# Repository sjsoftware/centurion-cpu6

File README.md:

# centurion-cpu6

* Schematic of the Centurion CPU6 board
* Schematic of the Centurion CPU5 boards
    * Original plus some revisions 
* Microcode disassembly (plus on wiki)
* Instruction reference (on wiki)
* Whatever I add in

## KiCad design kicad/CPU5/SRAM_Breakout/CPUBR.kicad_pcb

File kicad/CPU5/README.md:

# CPU 5 Reverse Engineering

Use at your own risk

The schematics are a bit of a mess, I wanted to get them to fit on A1 paper. If you have suggestions for
improvement, raise an issue.

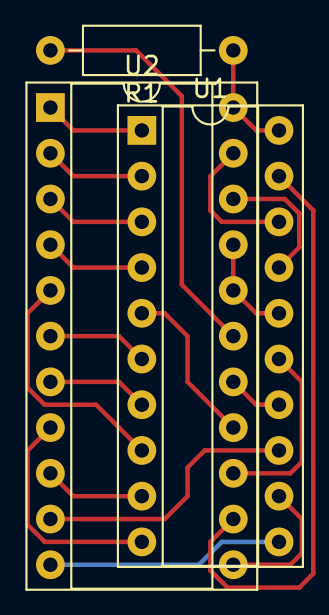
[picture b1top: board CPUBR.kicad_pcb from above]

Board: 2 copper layers, 3 parts (0 on the bottom side), 21 nets.

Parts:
R1: 1k; R_Axial_DIN0207_L6.3mm_D2.5mm_P10.16mm_Horizontal
U1: 74LS208; DIP-20_W7.62mm_Socket
U2: 93L422; DIP-22_W10.16mm_Socket

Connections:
GND: U1.10 (GND), U2.8 (GND)
unnamed: U1.11 (D0), U2.11 (D1)
unnamed: U1.14 (Q2), U2.16 (Q3)
unnamed: U1.16 (~OE), U2.18 (~OE), U2.19 (~CS1)
unnamed: U1.17 (WE), U2.20 (~WE)
unnamed: U1.18 (A7), U2.21 (A4)
unnamed: U1.19 (D3), U2.13 (D2)
unnamed: U1.1 (A0), U2.1 (A3)
unnamed: U1.2 (A1), U2.2 (A2)
unnamed: U1.3 (A2), U2.3 (A1)
unnamed: U1.4 (A3), U2.4 (A0)
unnamed: U1.8 (A6), U2.5 (A5)
unnamed: U1.6 (A4), U2.6 (A6)
unnamed: U1.7 (A5), U2.7 (A7)
unnamed: U1.9 (D1), U2.9 (D0)
unnamed: U1.13 (Q1), U2.10 (Q0)
unnamed: U1.12 (Q0), U2.12 (Q1)
unnamed: U1.15 (Q3), U2.14 (Q2)
unnamed: U1.5 (D2), U2.15 (D3)
unnamed: R1.2, U2.17 (CS2)
VCC: R1.1, U1.20 (VCC), U2.22 (VCC)

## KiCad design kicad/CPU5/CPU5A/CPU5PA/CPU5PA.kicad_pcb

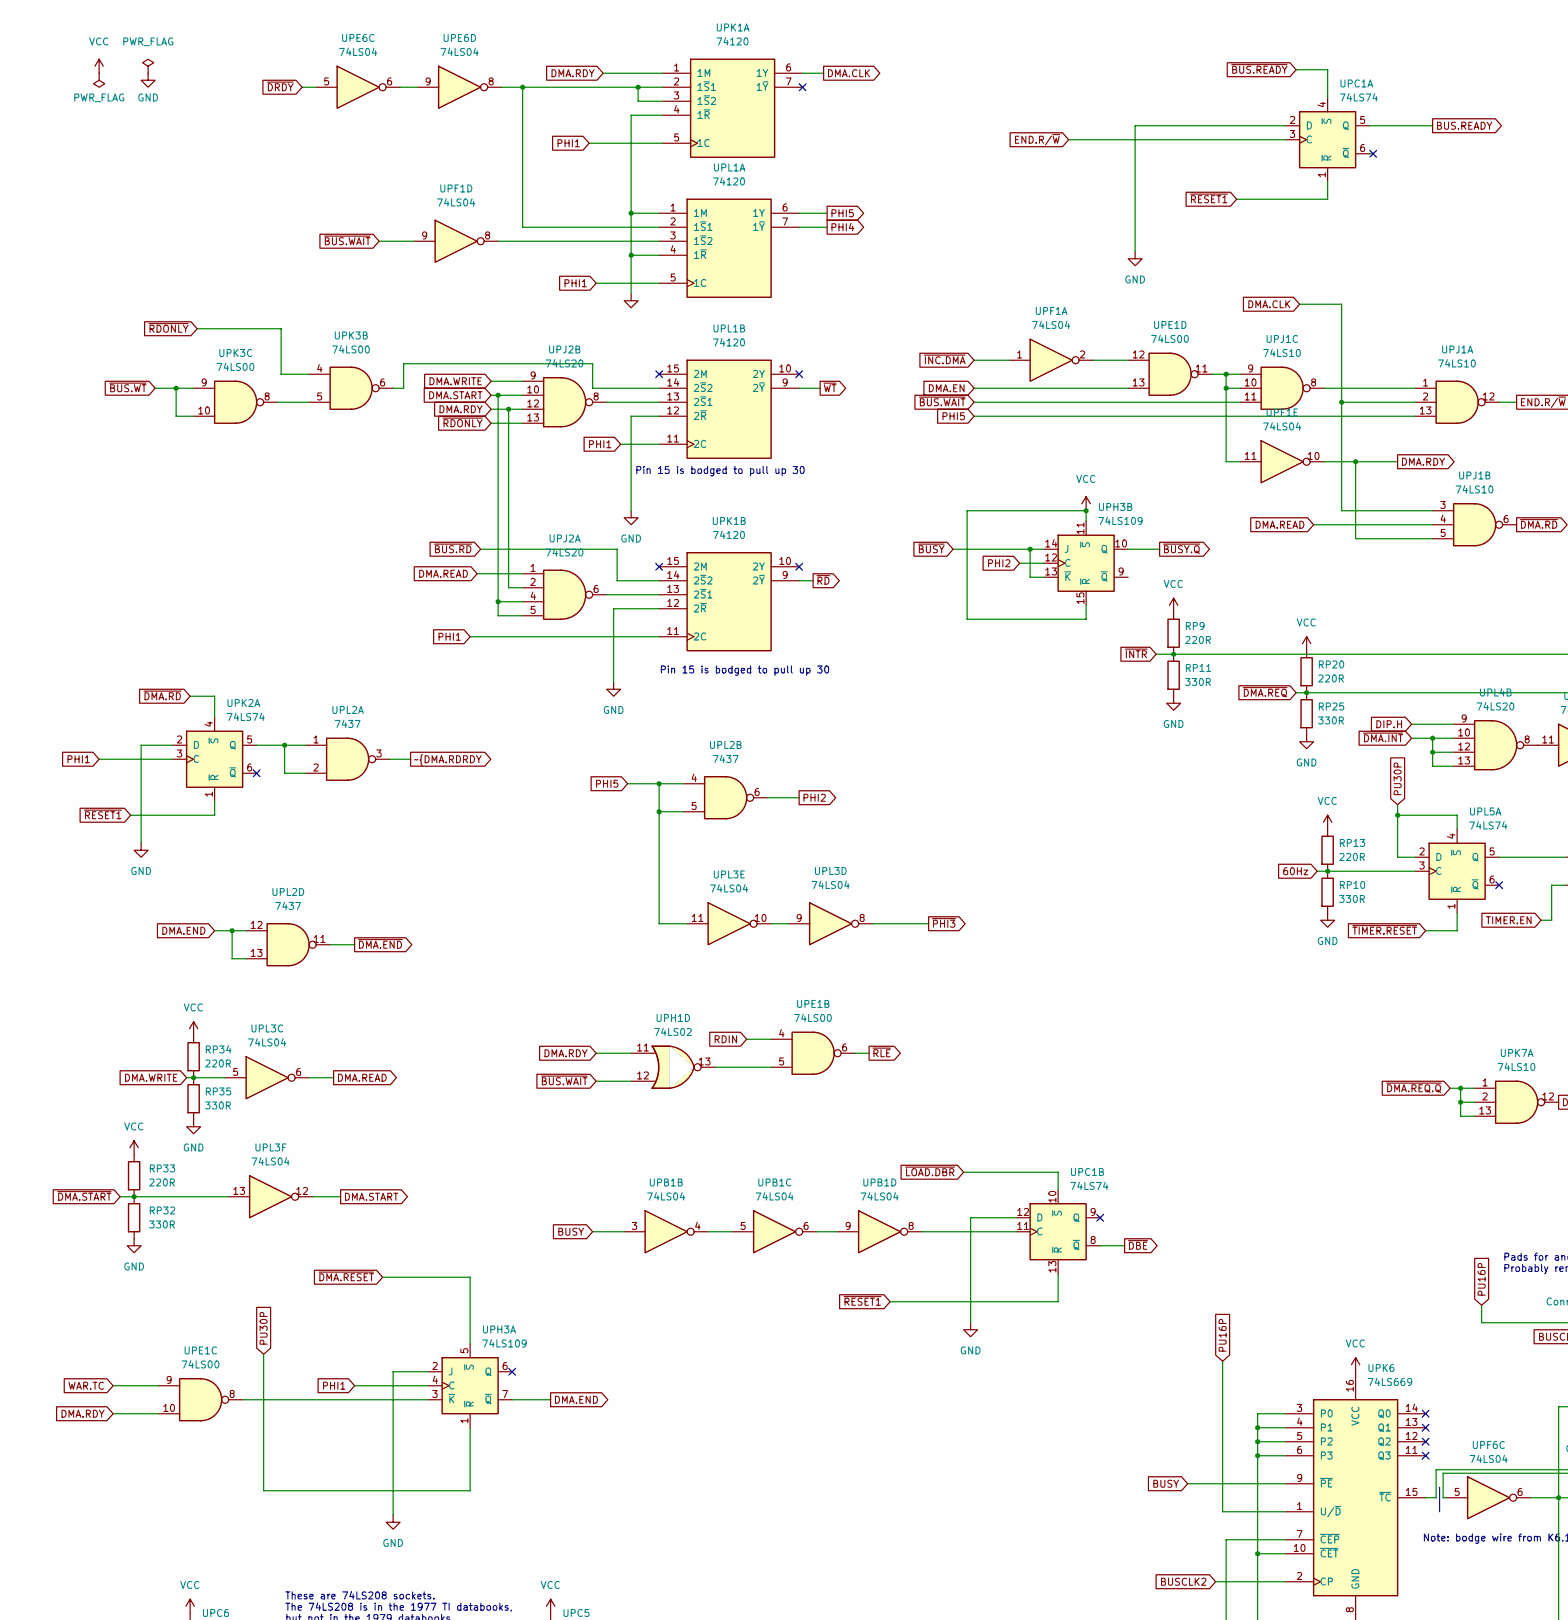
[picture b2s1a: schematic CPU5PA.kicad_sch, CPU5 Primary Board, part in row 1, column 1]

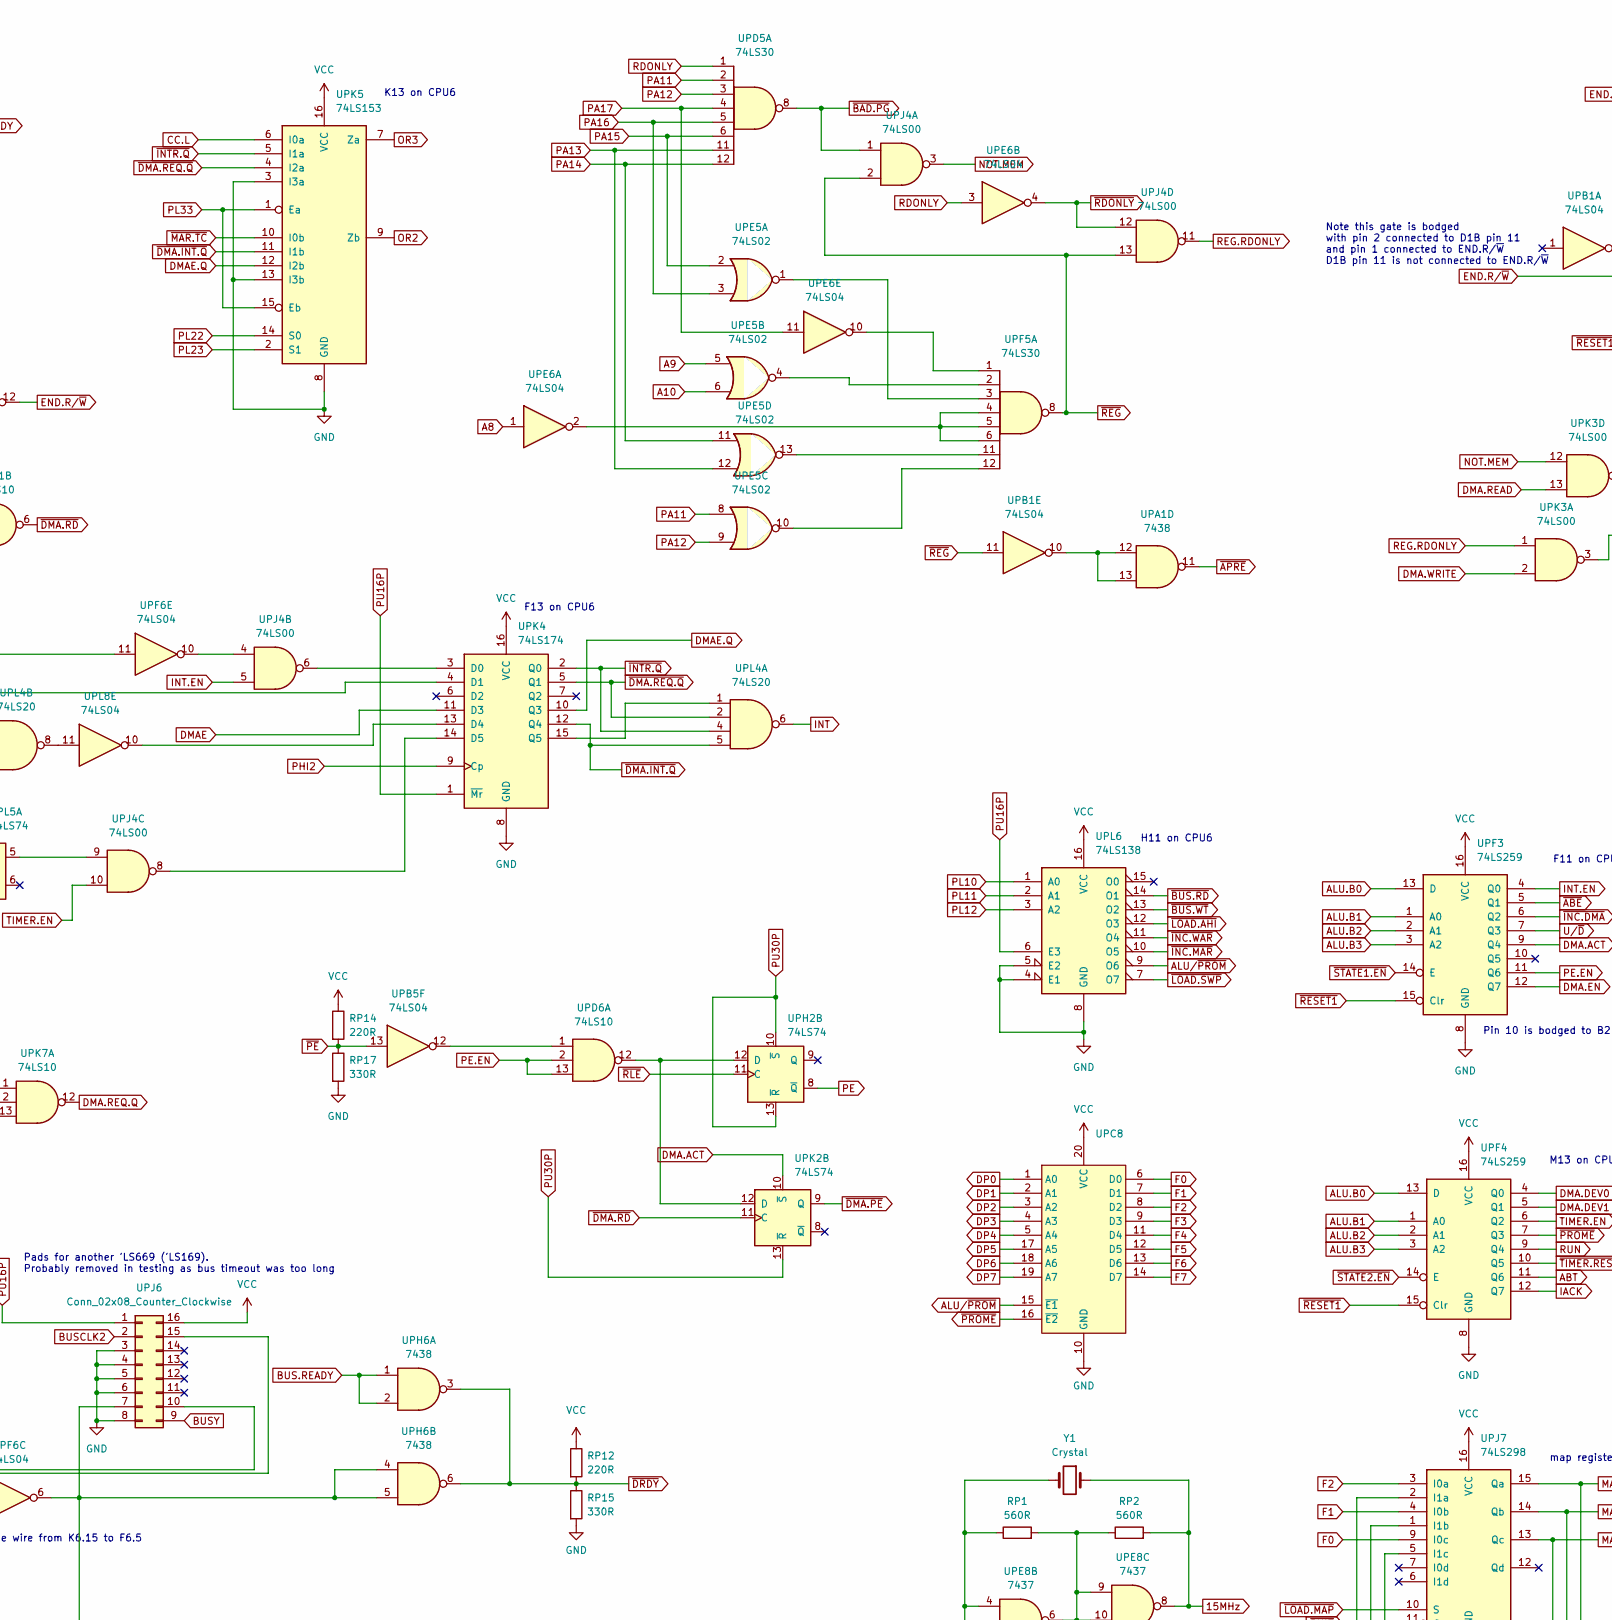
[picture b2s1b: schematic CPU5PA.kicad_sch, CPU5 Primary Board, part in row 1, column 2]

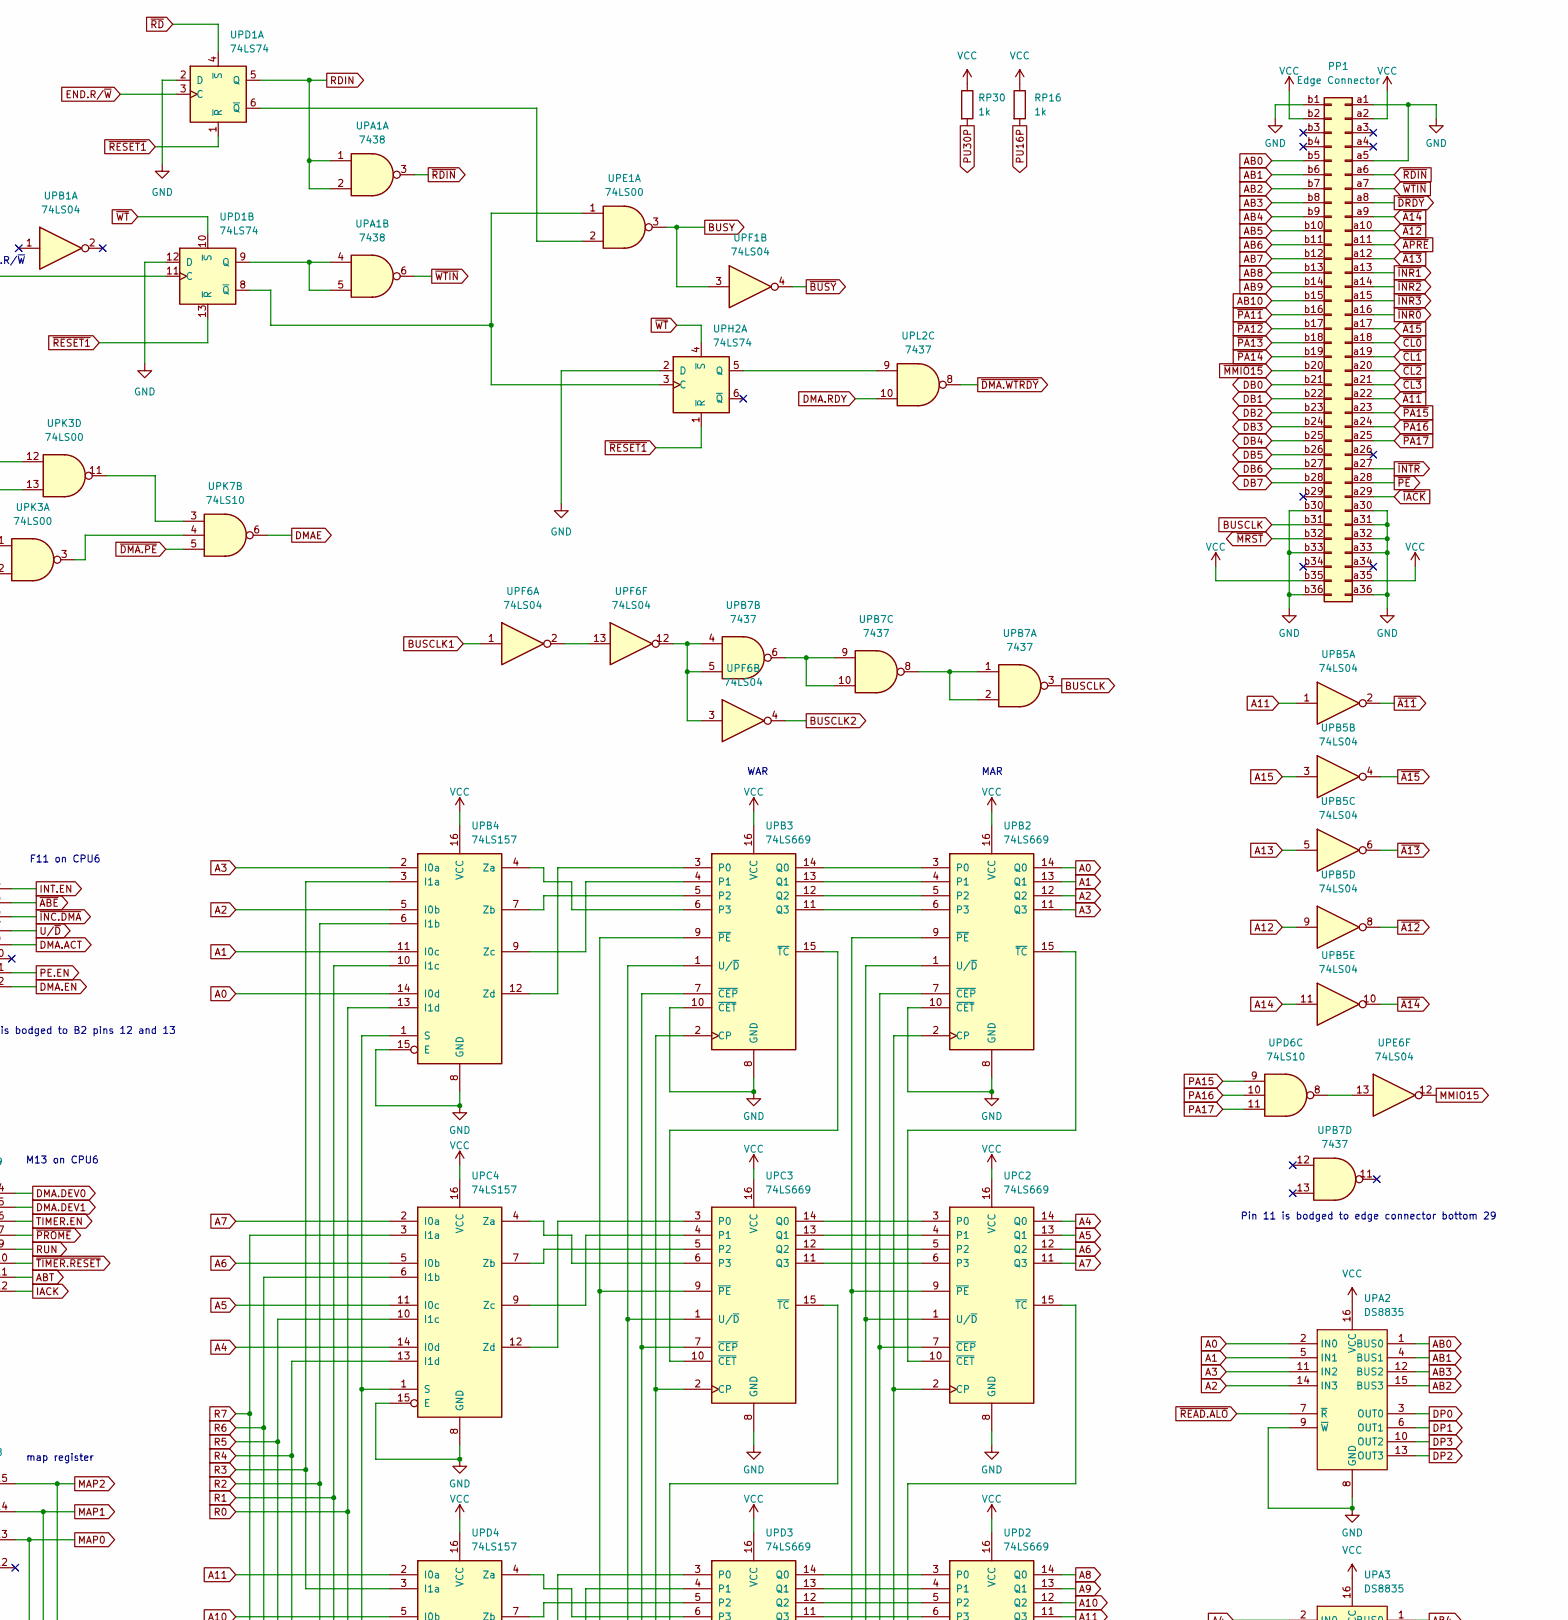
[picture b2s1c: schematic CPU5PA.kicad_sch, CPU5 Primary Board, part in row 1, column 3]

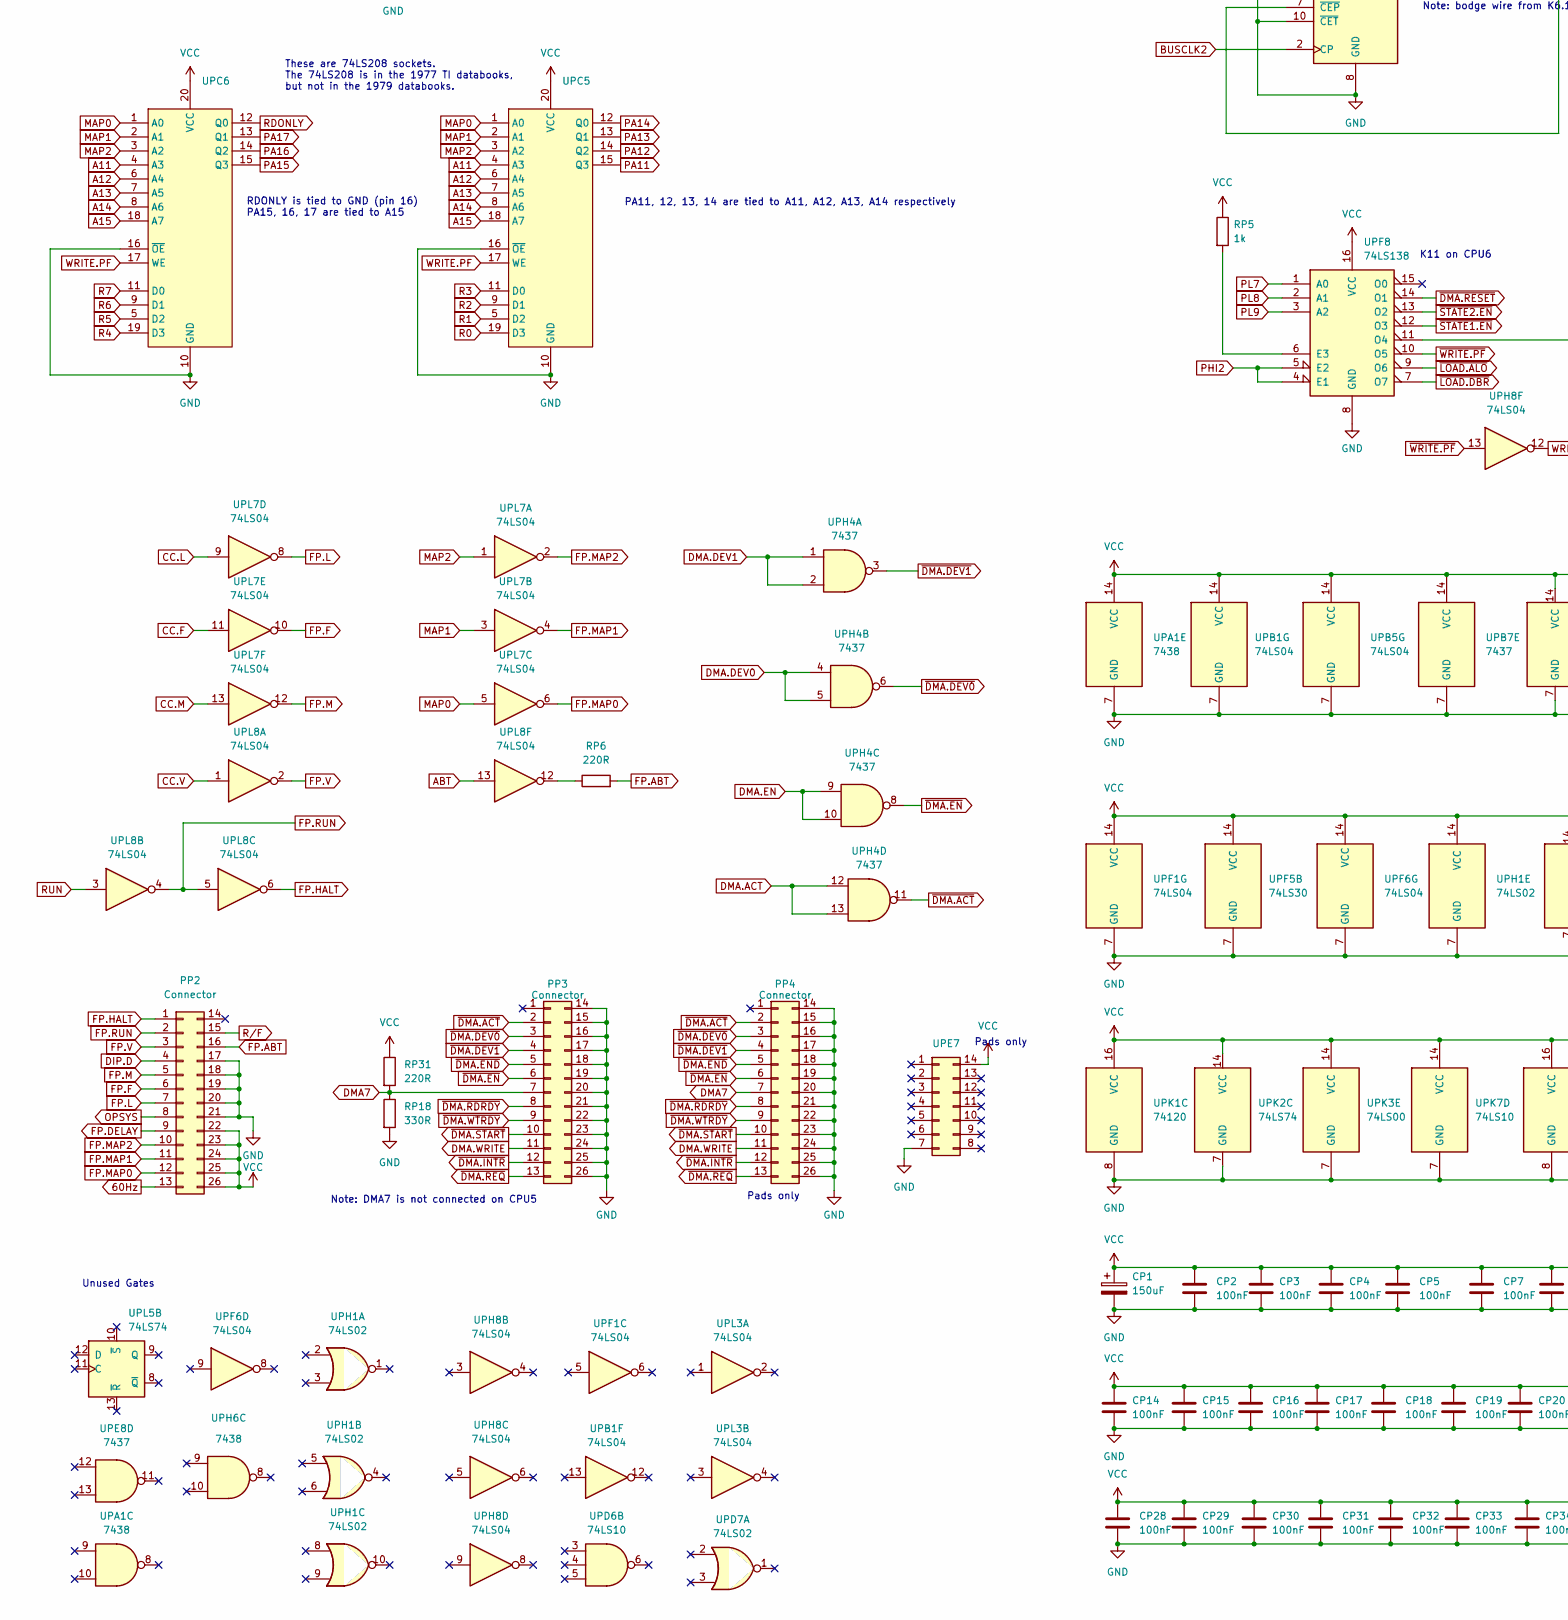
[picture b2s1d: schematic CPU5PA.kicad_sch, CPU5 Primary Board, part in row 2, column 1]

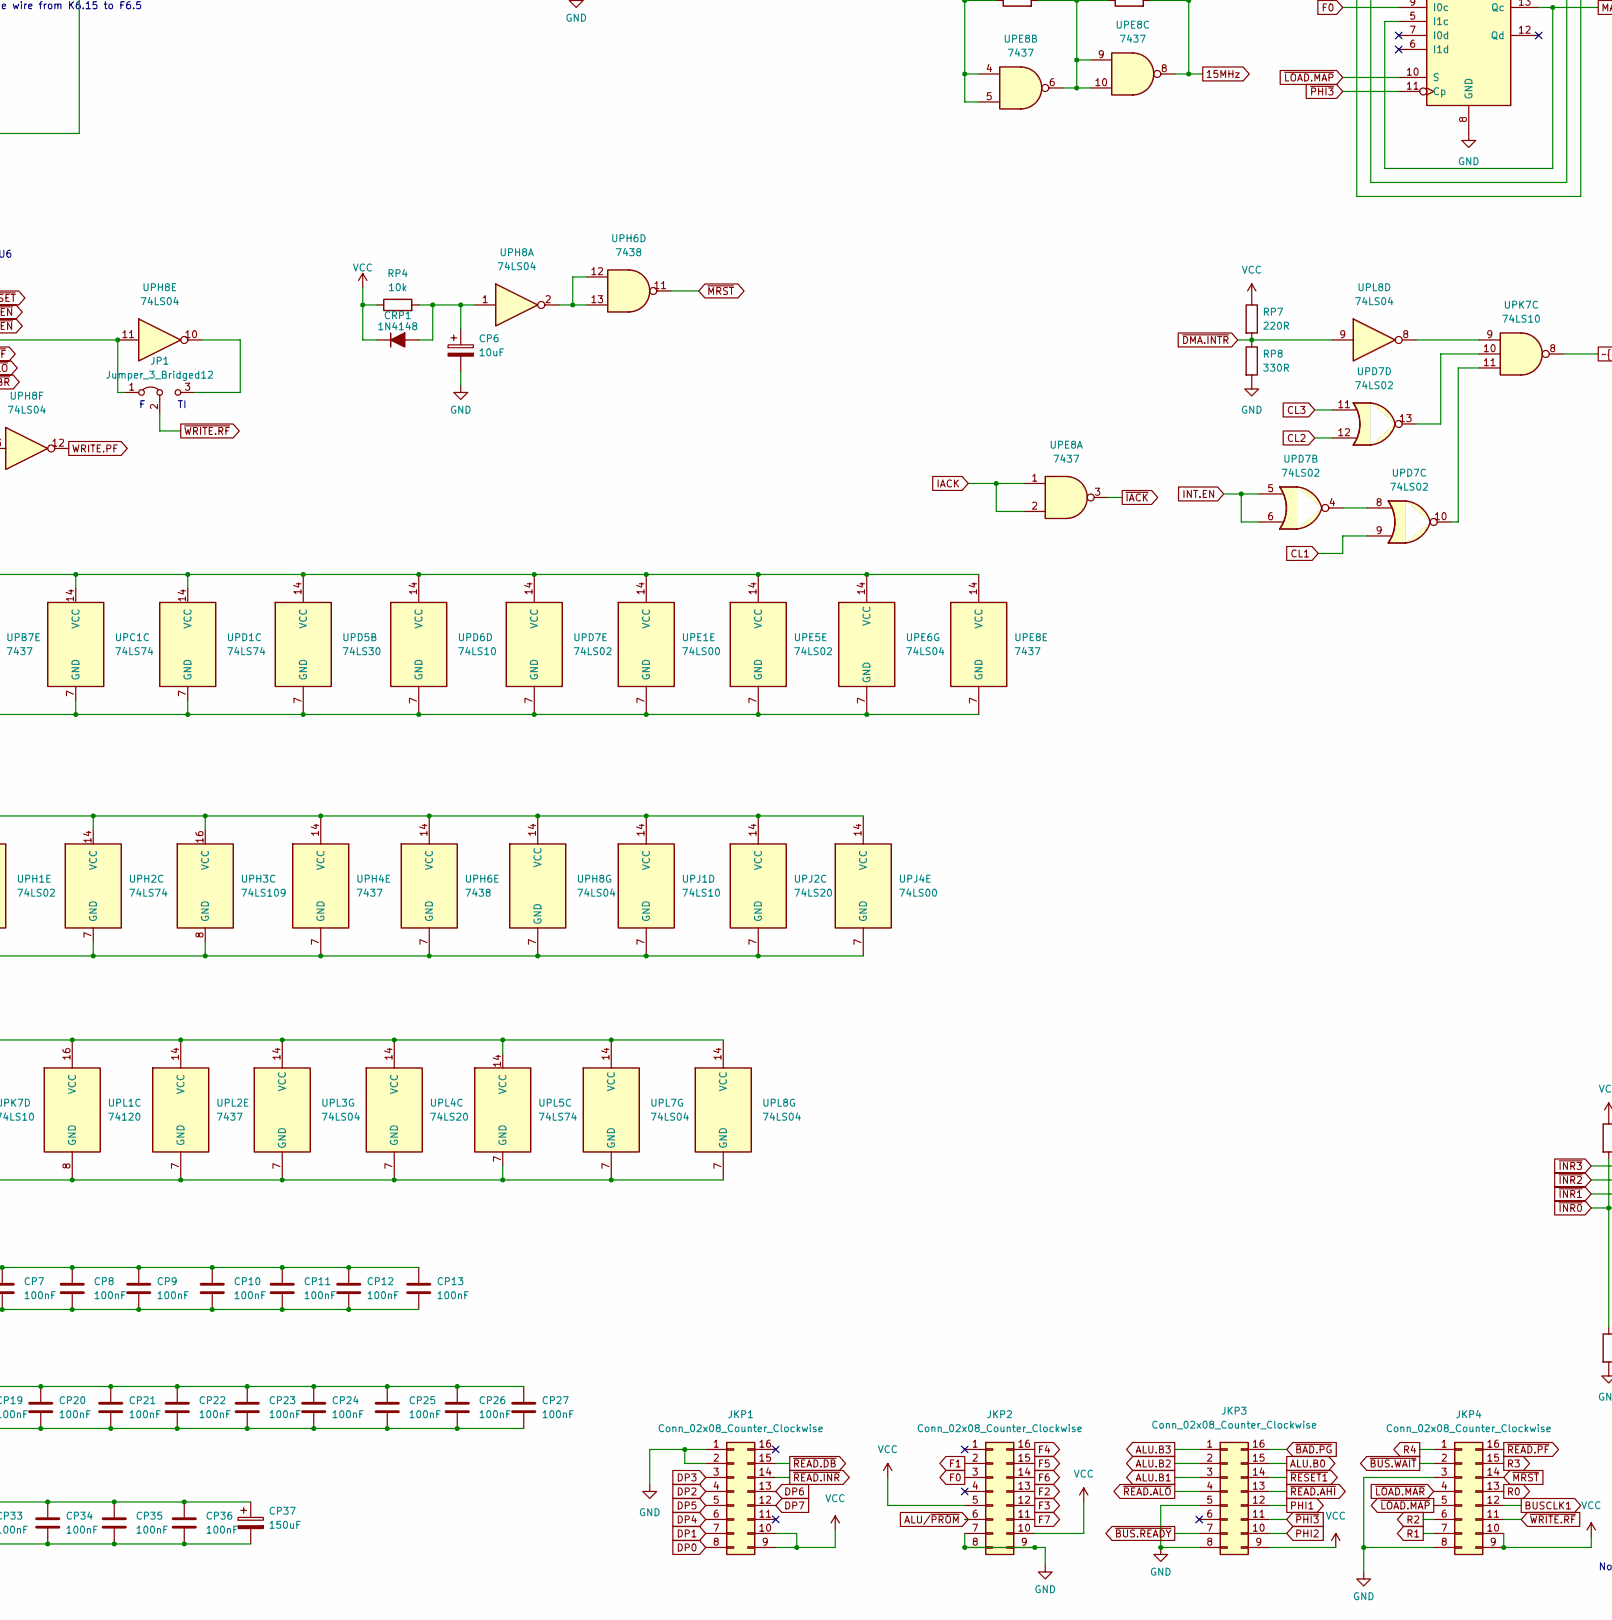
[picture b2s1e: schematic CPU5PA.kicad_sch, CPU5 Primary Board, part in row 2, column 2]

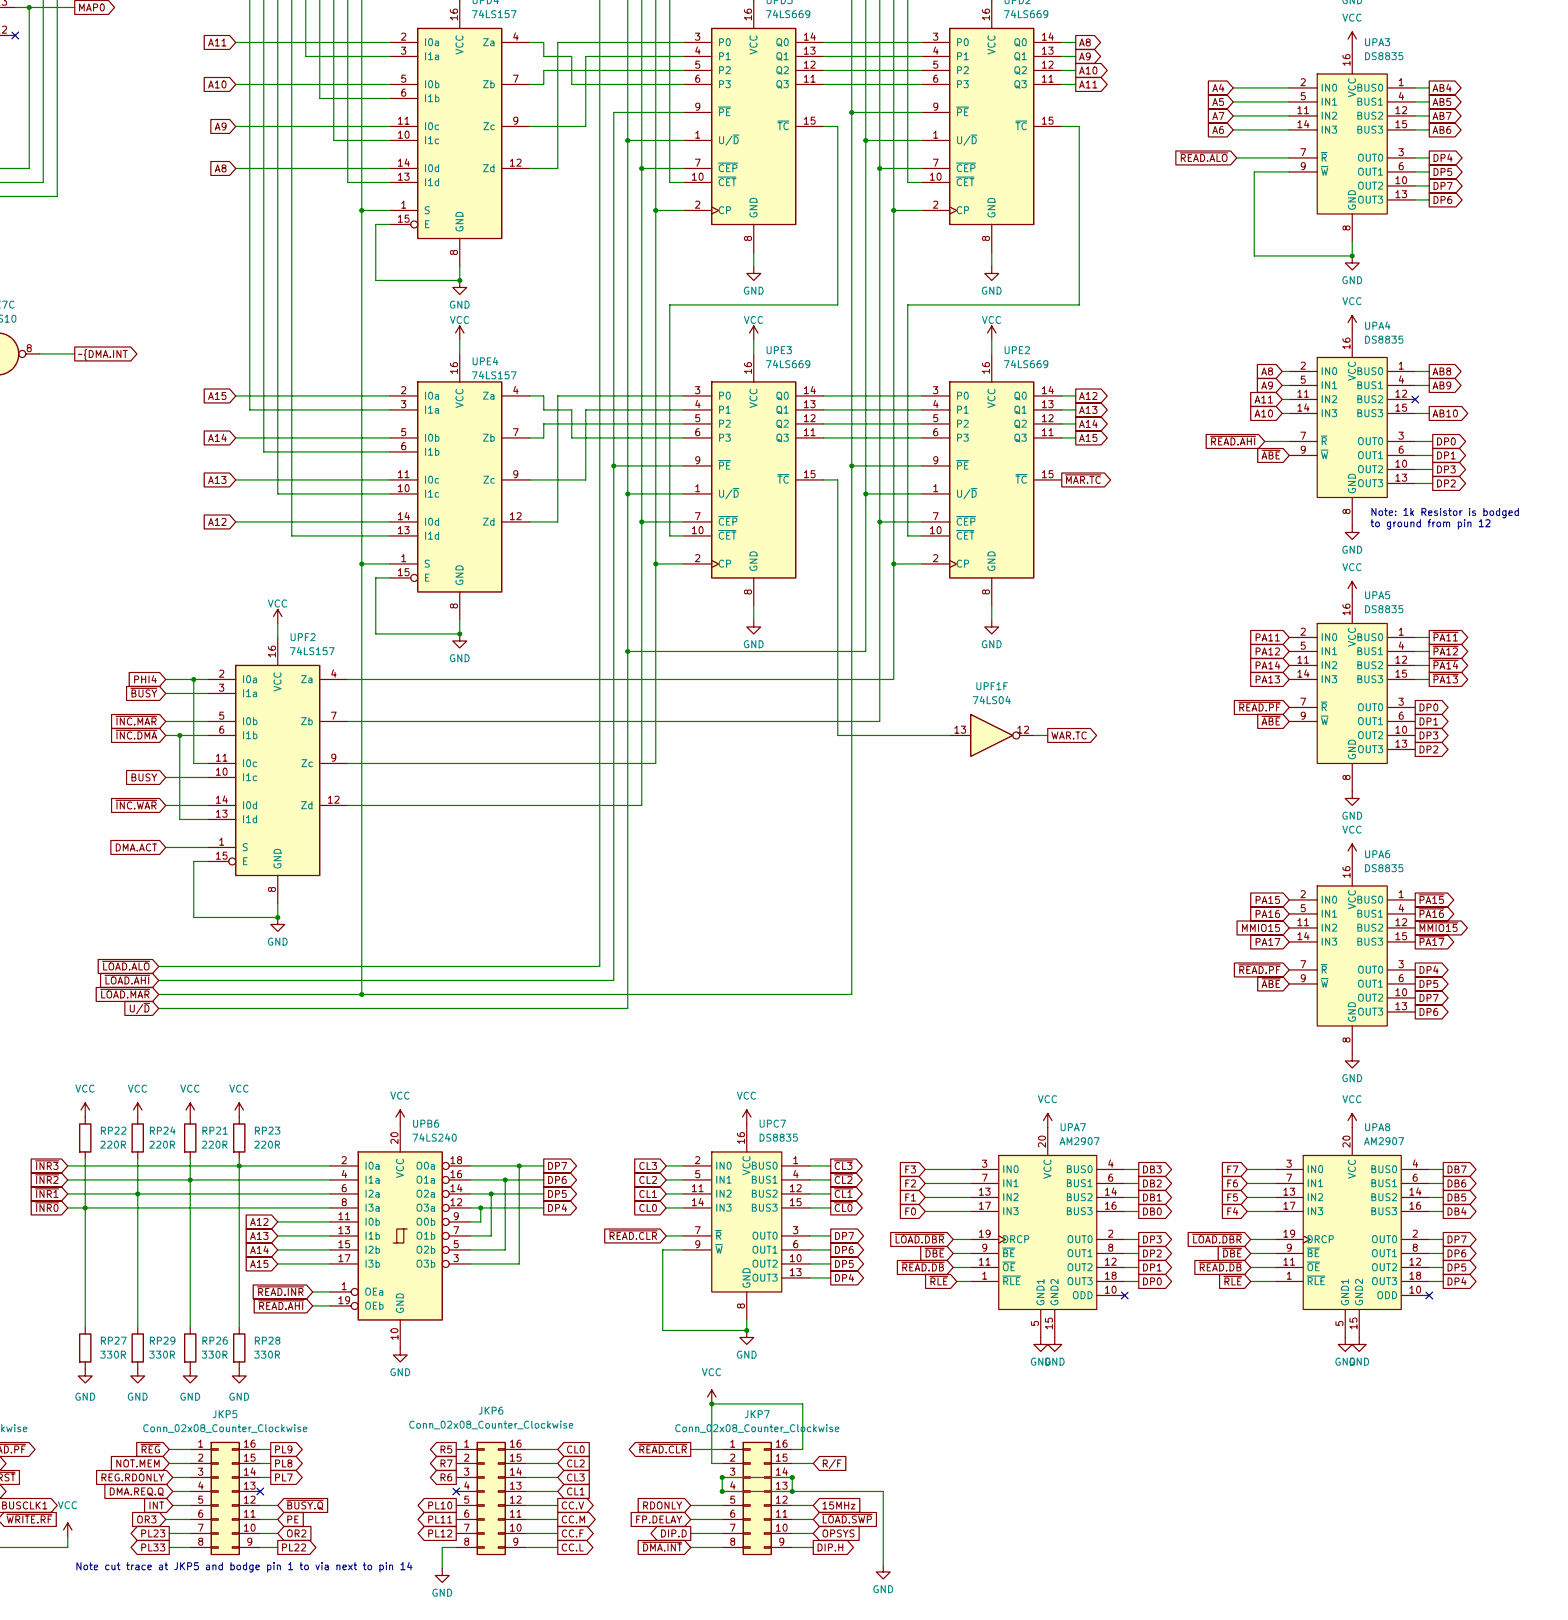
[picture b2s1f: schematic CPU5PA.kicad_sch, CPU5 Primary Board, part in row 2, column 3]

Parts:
CP1, CP37: 150uF; CP_Axial_L25.0mm_D10.0mm_P31.75mm_Horizontal
CP2, CP3, CP4, CP5, CP7, CP8, CP9, CP10, CP11, CP12, CP13, CP14, CP15, CP16, CP17, CP18, CP19, CP20, CP21, CP22, CP23, CP24, CP25, CP26, CP27, CP28, CP29, CP30, CP31, CP32, CP33, CP34, CP35, CP36: 100nF; C_Disc_D3.0mm_W1.6mm_P2.54mm
CP6: 10uF; CP_Axial_L18.0mm_D6.5mm_P26.67mm_Horizontal
CRP1: 1N4148; D_DO-35_SOD27_P11.43mm_Horizontal
JKP1, JKP2, JKP3, JKP4, JKP5, JKP6, JKP7: Conn_02x08_Counter_Clockwise; DIP-16_W7.62mm_cent_socket_ud
JP1: Jumper_3_Bridged12; Pads_1x03_P3.18mm
PP1: Edge Connector
PP2, PP3, PP4: Connector; IDC-Header_2x13_P2.54mm_Horizontal_TB
RP1, RP2: 560R; R_Axial_DIN0207_L6.3mm_D2.5mm_P11.43mm_Horizontal
RP4: 10k; R_Axial_DIN0207_L6.3mm_D2.5mm_P11.43mm_Horizontal
RP5, RP16, RP30: 1k; R_Axial_DIN0207_L6.3mm_D2.5mm_P11.43mm_Horizontal
RP6, RP7, RP9, RP12, RP13, RP14, RP20, RP21, RP22, RP23, RP24, RP31, RP33, RP34: 220R; R_Axial_DIN0207_L6.3mm_D2.5mm_P11.43mm_Horizontal
RP8, RP10, RP11, RP15, RP17, RP18, RP25, RP26, RP27, RP28, RP29, RP32, RP35: 330R; R_Axial_DIN0207_L6.3mm_D2.5mm_P11.43mm_Horizontal
UPA1: 7438; DIP-14_W7.62mm_cent
UPA2, UPA3, UPA4, UPA5, UPA6: DS8835; DIP-16_W7.62mm_cent
UPA7, UPA8: AM2907; DIP-20_W7.62mm_cent_socketchip
UPB1, UPB5: 74LS04; DIP-14_W7.62mm_cent
UPB2, UPB3: 74LS669; DIP-16_W7.62mm_cent
UPB4: 74LS157; DIP-16_W7.62mm_cent
UPB6: 74LS240; DIP-20_W7.62mm_cent
UPB7: 7437; DIP-14_W7.62mm_cent
UPC1: 74LS74; DIP-14_W7.62mm_cent
UPC2, UPC3: 74LS669; DIP-16_W7.62mm_cent
UPC4: 74LS157; DIP-16_W7.62mm_cent
UPC5, UPC6, UPC8: (no value)
UPC7: DS8835; DIP-16_W7.62mm_cent
UPD1: 74LS74; DIP-14_W7.62mm_cent
UPD2, UPD3: 74LS669; DIP-16_W7.62mm_cent
UPD4: 74LS157; DIP-16_W7.62mm_cent
UPD5: 74LS30; DIP-14_W7.62mm_cent
UPD6: 74LS10; DIP-14_W7.62mm_cent
UPD7: 74LS02; DIP-14_W7.62mm_cent
UPE1: 74LS00; DIP-14_W7.62mm_cent
UPE2, UPE3: 74LS669; DIP-16_W7.62mm_cent
UPE4: 74LS157; DIP-16_W7.62mm_cent
UPE5: 74LS02; DIP-14_W7.62mm_cent
UPE6: 74LS04; DIP-14_W7.62mm_cent
UPE7: Conn_02x07_Counter_Clockwise; DIP-14_W7.62mm_cent_padsonly
UPE8: 7437; DIP-14_W7.62mm_cent
UPF1, UPF6: 74LS04; DIP-14_W7.62mm_cent
UPF2: 74LS157; DIP-16_W7.62mm_cent
UPF3, UPF4: 74LS259; DIP-16_W7.62mm_cent
UPF5: 74LS30; DIP-14_W7.62mm_cent
UPF8: 74LS138; DIP-16_W7.62mm_cent
UPH1: 74LS02; DIP-14_W7.62mm_cent
UPH2: 74LS74; DIP-14_W7.62mm_cent
UPH3: 74LS109; DIP-16_W7.62mm_cent
UPH4: 7437; DIP-14_W7.62mm_cent
UPH6: 7438; DIP-14_W7.62mm_cent
UPH8: 74LS04; DIP-14_W7.62mm_cent
UPJ1: 74LS10; DIP-14_W7.62mm_cent
UPJ2: 74LS20; DIP-14_W7.62mm_cent
UPJ4: 74LS00; DIP-14_W7.62mm_cent
UPJ6: Conn_02x08_Counter_Clockwise; DIP-16_W7.62mm_cent_padsonly
UPJ7: 74LS298; DIP-16_W7.62mm_cent
UPK1: 74120; DIP-16_W7.62mm_cent
UPK2: 74LS74; DIP-14_W7.62mm_cent
UPK3: 74LS00; DIP-14_W7.62mm_cent
UPK4: 74LS174; DIP-16_W7.62mm_cent
UPK5: 74LS153; DIP-16_W7.62mm_cent
UPK6: 74LS669; DIP-16_W7.62mm_cent
UPK7: 74LS10; DIP-14_W7.62mm_cent
UPL1: 74120; DIP-16_W7.62mm_cent
UPL2: 7437; DIP-14_W7.62mm_cent
UPL3, UPL7, UPL8: 74LS04; DIP-14_W7.62mm_cent
UPL4: 74LS20; DIP-14_W7.62mm_cent
UPL5: 74LS74; DIP-14_W7.62mm_cent
UPL6: 74LS138; DIP-16_W7.62mm_cent
Y1: Crystal; Crystal_HC49-U_Horizontal_P5.08mm

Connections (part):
15MHz: JKP7.12, RP2.2, UPE8.8, Y1.1
60Hz: PP2.13, RP10.1, RP13.2, UPL5.3 (C)
A0: UPA2.2 (IN0), UPB2.14 (Q0), UPB4.14 (I0d)
A1: UPA2.5 (IN1), UPB2.13 (Q1), UPB4.11 (I0c)
A2: UPA2.14 (IN3), UPB2.12 (Q2), UPB4.5 (I0b)
A3: UPA2.11 (IN2), UPB2.11 (Q3), UPB4.2 (I0a)
A4: UPA3.2 (IN0), UPC2.14 (Q0), UPC4.14 (I0d)
A5: UPA3.5 (IN1), UPC2.13 (Q1), UPC4.11 (I0c)
A6: UPA3.14 (IN3), UPC2.12 (Q2), UPC4.5 (I0b)
A7: UPA3.11 (IN2), UPC2.11 (Q3), UPC4.2 (I0a)
A8: UPA4.2 (IN0), UPD2.14 (Q0), UPD4.14 (I0d), UPE6.1
A9: UPA4.5 (IN1), UPD2.13 (Q1), UPD4.11 (I0c), UPE5.5
A10: UPA4.14 (IN3), UPD2.12 (Q2), UPD4.5 (I0b), UPE5.6
A11: UPA4.11 (IN2), UPB5.1, UPC5.4 (A3), UPC6.4 (A3), UPD2.11 (Q3), UPD4.2 (I0a)
A12: UPB5.9, UPB6.11 (I0b), UPC5.6 (A4), UPC6.6 (A4), UPE2.14 (Q0), UPE4.14 (I0d)
A13: UPB5.5, UPB6.13 (I1b), UPC5.7 (A5), UPC6.7 (A5), UPE2.13 (Q1), UPE4.11 (I0c)
A14: UPB5.11, UPB6.15 (I2b), UPC5.8 (A6), UPC6.8 (A6), UPE2.12 (Q2), UPE4.5 (I0b)
A15: UPB5.3, UPB6.17 (I3b), UPC5.18 (A7), UPC6.18 (A7), UPE2.11 (Q3), UPE4.2 (I0a)
AB0: PP1.b5, UPA2.1 (BUS0)
AB1: PP1.b6, UPA2.4 (BUS1)
AB2: PP1.b7, UPA2.15 (BUS3)
AB3: PP1.b8, UPA2.12 (BUS2)
AB4: PP1.b9, UPA3.1 (BUS0)
AB5: PP1.b10, UPA3.4 (BUS1)
AB6: PP1.b11, UPA3.15 (BUS3)
AB7: PP1.b12, UPA3.12 (BUS2)
AB8: PP1.b13, UPA4.1 (BUS0)
AB9: PP1.b14, UPA4.4 (BUS1)
AB10: PP1.b15, UPA4.15 (BUS3)
ABT: UPF4.11 (Q6), UPL8.13
ALU.B0: JKP3.15, UPF3.13 (D), UPF4.13 (D)
ALU.B1: JKP3.3, UPF3.1 (A0), UPF4.1 (A0)
ALU.B2: JKP3.2, UPF3.2 (A1), UPF4.2 (A1)
ALU.B3: JKP3.1, UPF3.3 (A2), UPF4.3 (A2)
ALU/~PROM: JKP2.6, UPC8.15 (~E1), UPL6.9 (O6)
BUS.READY: UPC1.5 (Q), UPH6.1, UPH6.2
BUSCLK: PP1.b31, UPB7.3
BUSCLK1: JKP4.12, UPF6.1
BUSCLK2: UPF6.4, UPJ6.2, UPK6.2 (CP)
BUSY: UPB1.3, UPE1.3, UPF1.3, UPF2.10 (I1c), UPJ6.9, UPK6.9 (~PE)
CC.F: JKP6.10, UPL7.11
CC.L: JKP6.9, UPK5.6 (I0a), UPL7.9
CC.M: JKP6.11, UPL7.13
CC.V: JKP6.12, UPL8.1
CL0: JKP6.16, UPC7.14 (IN3)
CL1: JKP6.13, UPC7.11 (IN2), UPD7.9
CL2: JKP6.15, UPC7.5 (IN1), UPD7.12
CL3: JKP6.14, UPC7.2 (IN0), UPD7.11
DB0: PP1.b21, UPA7.16 (BUS3)
DB1: PP1.b22, UPA7.14 (BUS2)
DB2: PP1.b23, UPA7.6 (BUS1)
DB3: PP1.b24, UPA7.4 (BUS0)
DB4: PP1.b25, UPA8.16 (BUS3)
DB5: PP1.b26, UPA8.14 (BUS2)
DB6: PP1.b27, UPA8.6 (BUS1)
DB7: PP1.b28, UPA8.4 (BUS0)
DIP.D: JKP7.7, PP2.4
DIP.H: JKP7.9, UPL4.9
DMA7: PP3.7, PP4.7, RP18.1, RP31.2
DMA.ACT: UPF2.1 (S), UPF3.9 (Q4), UPH4.12, UPH4.13, UPK2.10 (~S)
DMA.CLK: UPJ1.2, UPJ1.3, UPK1.6 (1Y)
DMA.DEV0: UPF4.4 (Q0), UPH4.4, UPH4.5
DMA.DEV1: UPF4.5 (Q1), UPH4.1, UPH4.2
DMA.EN: UPE1.13, UPF3.12 (Q7), UPH4.9, UPH4.10
DMA.END: UPH3.7 (~Q), UPL2.12, UPL2.13
DMA.RDY: UPE1.10, UPF1.10, UPH1.11, UPJ1.5, UPJ2.2, UPJ2.12, UPK1.1 (1M), UPL2.10
DMA.READ: UPJ1.4, UPJ2.1, UPK3.13, UPL3.6
DMA.REQ.Q: JKP5.4, UPK7.12
DMA.START: UPJ2.4, UPJ2.5, UPJ2.10, UPL3.12
DMA.WRITE: PP3.11, PP4.11, RP34.2, RP35.1, UPJ2.9, UPK3.2, UPL3.5
DMAE: UPK4.11 (D3), UPK7.6
DMAE.Q: UPK4.10 (Q3), UPK5.12 (I2b)
DP0: JKP1.8, UPA2.3 (OUT0), UPA4.3 (OUT0), UPA5.3 (OUT0), UPA7.18 (OUT3), UPC8.1 (A0)
DP1: JKP1.7, UPA2.6 (OUT1), UPA4.6 (OUT1), UPA5.6 (OUT1), UPA7.12 (OUT2), UPC8.2 (A1)
DP2: JKP1.4, UPA2.13 (OUT3), UPA4.13 (OUT3), UPA5.13 (OUT3), UPA7.8 (OUT1), UPC8.3 (A2)
DP3: JKP1.3, UPA2.10 (OUT2), UPA4.10 (OUT2), UPA5.10 (OUT2), UPA7.2 (OUT0), UPC8.4 (A3)
DP4: JKP1.6, UPA3.3 (OUT0), UPA6.3 (OUT0), UPA8.18 (OUT3), UPB6.9 (O0b), UPB6.12 (O3a), UPC7.13 (OUT3), UPC8.5 (A4)
DP5: JKP1.5, UPA3.6 (OUT1), UPA6.6 (OUT1), UPA8.12 (OUT2), UPB6.7 (O1b), UPB6.14 (O2a), UPC7.10 (OUT2), UPC8.17 (A5)
DP6: JKP1.13, UPA3.13 (OUT3), UPA6.13 (OUT3), UPA8.8 (OUT1), UPB6.5 (O2b), UPB6.16 (O1a), UPC7.6 (OUT1), UPC8.18 (A6)
DP7: JKP1.12, UPA3.10 (OUT2), UPA6.10 (OUT2), UPA8.2 (OUT0), UPB6.3 (O3b), UPB6.18 (O0a), UPC7.3 (OUT0), UPC8.19 (A7)
END.R/~W: UPC1.3 (C), UPD1.3 (C), UPD1.11 (C), UPJ1.12
F0: JKP2.3, UPA7.17 (IN3), UPC8.6 (D0), UPJ7.9 (I0c)
F1: JKP2.2, UPA7.13 (IN2), UPC8.7 (D1), UPJ7.4 (I0b)
F2: JKP2.13, UPA7.7 (IN1), UPC8.8 (D2), UPJ7.3 (I0a)
F3: JKP2.12, UPA7.3 (IN0), UPC8.9 (D3)
F4: JKP2.16, UPA8.17 (IN3), UPC8.11 (D4)
F5: JKP2.15, UPA8.13 (IN2), UPC8.12 (D5)
F6: JKP2.14, UPA8.7 (IN1), UPC8.13 (D6)
F7: JKP2.11, UPA8.3 (IN0), UPC8.14 (D7)
FP.ABT: PP2.16, RP6.2
FP.DELAY: JKP7.6, PP2.9
FP.F: PP2.6, UPL7.10
FP.HALT: PP2.1, UPL8.6
FP.L: PP2.7, UPL7.8
FP.M: PP2.5, UPL7.12
FP.MAP0: PP2.12, UPL7.6
FP.MAP1: PP2.11, UPL7.4
FP.MAP2: PP2.10, UPL7.2
FP.RUN: PP2.2, UPL8.4, UPL8.5
FP.V: PP2.3, UPL8.2
IACK: UPE8.1, UPE8.2, UPF4.12 (Q7)
INT: JKP5.5, UPL4.6
INT.EN: UPD7.5, UPD7.6, UPF3.4 (Q0), UPJ4.5
MAP0: UPC5.1 (A0), UPC6.1 (A0), UPJ7.5 (I1c), UPJ7.13 (Qc), UPL7.5
MAP1: UPC5.2 (A1), UPC6.2 (A1), UPJ7.1 (I1b), UPJ7.14 (Qb), UPL7.3
MAP2: UPC5.3 (A2), UPC6.3 (A2), UPJ7.2 (I1a), UPJ7.15 (Qa), UPL7.1
MMIO15: UPA6.11 (IN2), UPE6.12
NOT.MEM: JKP5.2, UPJ4.3, UPK3.12
unnamed: CP6.1, CRP1.2 (A), RP4.2, UPH8.1
unnamed: JP1.1 (A), UPF8.11 (O4), UPH8.11
unnamed: JP1.3 (B), UPH8.10
unnamed: RP1.1, UPE8.4, UPE8.5, Y1.2
unnamed: RP1.2, RP2.1, UPE8.6, UPE8.9, UPE8.10
unnamed: RP5.2, UPF8.6 (E3)
unnamed: RP6.1, UPL8.12
unnamed: UPA1.4, UPA1.5, UPD1.9 (Q)
unnamed: UPA1.12, UPA1.13, UPB1.10
unnamed: UPB1.4, UPB1.5
unnamed: UPB1.6, UPB1.9
unnamed: UPB1.8, UPC1.11 (C)
unnamed: UPB2.2 (CP), UPC2.2 (CP), UPD2.2 (CP), UPE2.2 (CP), UPF2.4 (Za)
unnamed: UPB2.3 (P0), UPB3.14 (Q0)
unnamed: UPB2.4 (P1), UPB3.13 (Q1)
unnamed: UPB2.5 (P2), UPB3.12 (Q2)
unnamed: UPB2.6 (P3), UPB3.11 (Q3)
unnamed: UPB2.7 (~CEP), UPC2.7 (~CEP), UPD2.7 (~CEP), UPE2.7 (~CEP), UPF2.7 (Zb)
unnamed: UPB2.15 (~TC), UPC2.10 (~CET)
unnamed: UPB3.2 (CP), UPC3.2 (CP), UPD3.2 (CP), UPE3.2 (CP), UPF2.9 (Zc)
unnamed: UPB3.3 (P0), UPB4.12 (Zd)
unnamed: UPB3.4 (P1), UPB4.9 (Zc)
unnamed: UPB3.5 (P2), UPB4.7 (Zb)
unnamed: UPB3.6 (P3), UPB4.4 (Za)
unnamed: UPB3.7 (~CEP), UPC3.7 (~CEP), UPD3.7 (~CEP), UPE3.7 (~CEP), UPF2.12 (Zd)
unnamed: UPB3.15 (~TC), UPC3.10 (~CET)
unnamed: UPB5.12, UPD6.1
unnamed: UPB7.1, UPB7.2, UPB7.8
unnamed: UPB7.4, UPB7.5, UPF6.3, UPF6.12
unnamed: UPB7.6, UPB7.9, UPB7.10
unnamed: UPC2.3 (P0), UPC3.14 (Q0)
unnamed: UPC2.4 (P1), UPC3.13 (Q1)
unnamed: UPC2.5 (P2), UPC3.12 (Q2)
unnamed: UPC2.6 (P3), UPC3.11 (Q3)
unnamed: UPC2.15 (~TC), UPD2.10 (~CET)
unnamed: UPC3.3 (P0), UPC4.12 (Zd)
unnamed: UPC3.4 (P1), UPC4.9 (Zc)
unnamed: UPC3.5 (P2), UPC4.7 (Zb)
unnamed: UPC3.6 (P3), UPC4.4 (Za)
unnamed: UPC3.15 (~TC), UPD3.10 (~CET)
unnamed: UPD1.6 (~Q), UPE1.2
unnamed: UPD1.8 (~Q), UPE1.1, UPH2.3 (C)
unnamed: UPD2.3 (P0), UPD3.14 (Q0)
unnamed: UPD2.4 (P1), UPD3.13 (Q1)
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
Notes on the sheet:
Note this gate is bodged with pin 2 connected to D1B pin 11 and pin 1 connected to END.R/~{W} D1B pin 11 is not connected to END.R/~{W}
Note: 1k Resistor is bodged to ground from pin 12
K11 on CPU6
map register
F11 on CPU6
RDONLY is tied to GND (pin 16) PA15, 16, 17 are tied to A15
Pads for another 'LS669 ('LS169). Probably removed in testing as bus timeout was too long
WAR
Note: bodge wire from K6.15 to F6.5
These are 74LS208 sockets. The 74LS208 is in the 1977 TI databooks, but not in the 1979 databooks.
Pin 10 is bodged to B2 pins 12 and 13
Note: DMA7 is not connected on CPU5
Pin 15 is bodged to pull up 30
Pin 11 is bodged to edge connector bottom 29
Note cut trace at JKP5 and bodge pin 1 to via next to pin 14
MAR
H11 on CPU6
Pads only
M13 on CPU6
Unused Gates
K13 on CPU6
PA11, 12, 13, 14 are tied to A11, A12, A13, A14 respectively
F13 on CPU6

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
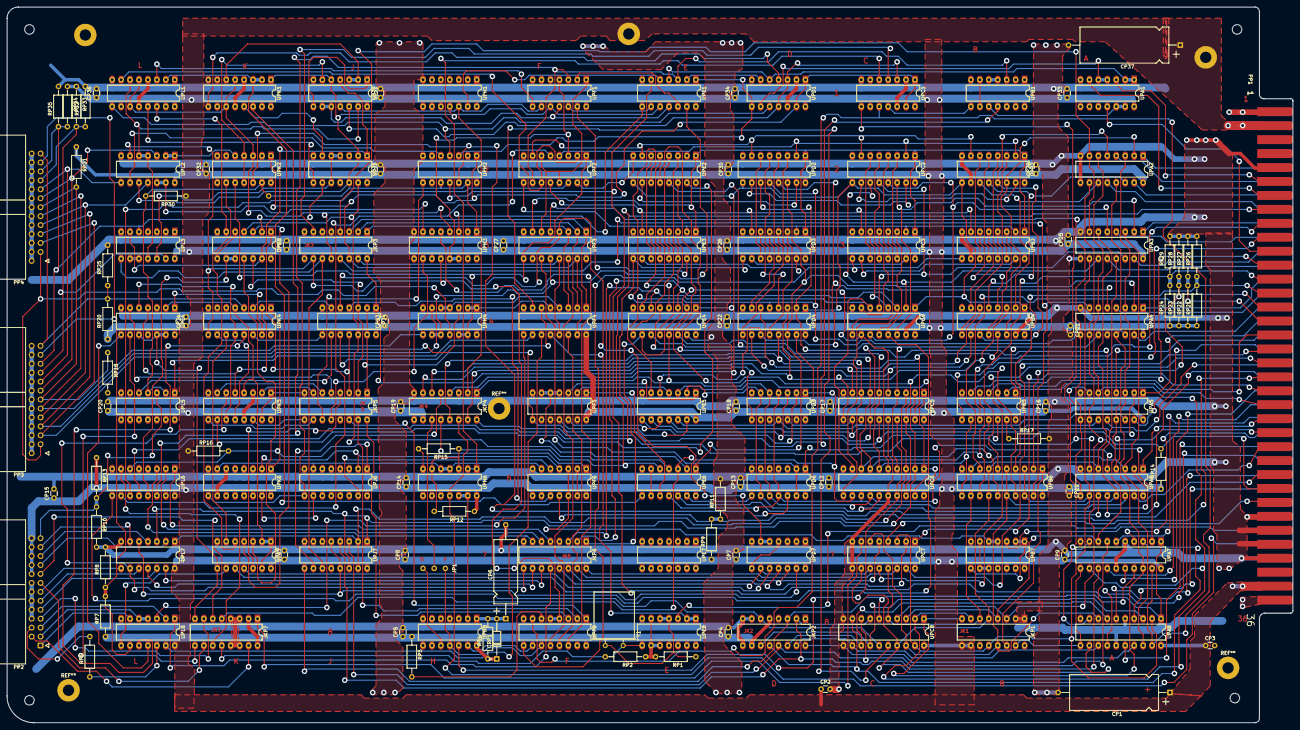
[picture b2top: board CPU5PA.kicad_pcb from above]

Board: 2 copper layers, 365.1 x 203.2 mm, 155 parts (0 on the bottom side), 340 nets.
